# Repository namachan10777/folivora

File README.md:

# Folivora

Integrated ergonomics input device.

# Dependencies
 * KiCAD
 * OCaml
 * OpenSCAD

# License
MIT License

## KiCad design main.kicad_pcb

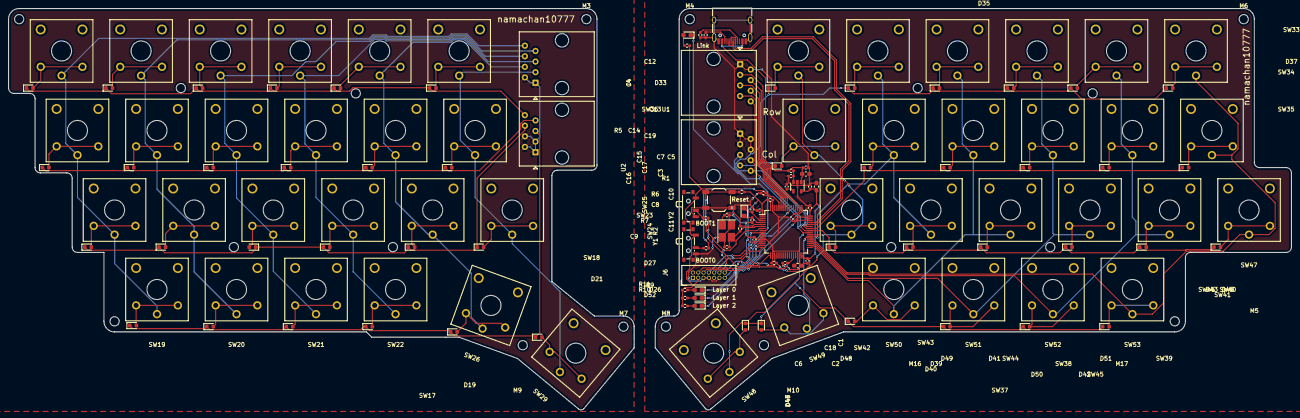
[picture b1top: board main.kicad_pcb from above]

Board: 2 copper layers, 307.3 x 96.1 mm, 161 parts (0 on the bottom side), 108 nets.

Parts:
C1, C3, C4, C5, C6, C7, C13, C14, C16, C18, C19: 0.1uF; C_0402_1005Metric_Pad0.74x0.62mm_HandSolder
C2, C12, C17: 4.7uF; C_0603_1608Metric_Pad1.08x0.95mm_HandSolder
C8, C9: 20pF; C_0402_1005Metric_Pad0.74x0.62mm_HandSolder
C10, C11: 12.5pF; C_0402_1005Metric_Pad0.74x0.62mm_HandSolder
C15: 0.1nF; C_0402_1005Metric_Pad0.74x0.62mm_HandSolder
D1, D2, D3, D4, D5, D6, D7, D8, D9, D10, D11, D12, D13, D14, D15, D16, D17, D18, D19, D20, D21, D22, D23, D24, D28, D29, D30, D31, D32, D33, D34, D35, D36, D37, D38, D39, D40, D41, D42, D43, D44, D45, D46, D47, D48, D49, D50, D51: D; D_0603_1608Metric
D25: LINKUP; LED_0603_1608Metric_Pad1.05x0.95mm_HandSolder
D26: L0; LED_0603_1608Metric_Pad1.05x0.95mm_HandSolder
D27: L1; LED_0603_1608Metric_Pad1.05x0.95mm_HandSolder
D52: L2; LED_0603_1608Metric_Pad1.05x0.95mm_HandSolder
J1, J2, J3, J4: RJ45; RJ45_Amphenol_54602-x08_Horizontal
J5: USB_C_Receptacle_USB2.0; USB_C_Receptacle_HRO_TYPE-C-31-M-12
J6: STLinkV3; IDC-Header_2x07_P1.27mm_Vertical
M1, M2, M3, M4, M5, M6, M7, M8, M9, M10, M11, M12, M13, M14, M15, M16, M17: MountingHole_2.2mm_M2
M20: MountingHole_2.2mm_M; MountingHole_2.2mm_M2
R1, R5, R6, R7: 10kohm; R_0402_1005Metric_Pad0.72x0.64mm_HandSolder
R2: 10Mohm; R_0402_1005Metric_Pad0.72x0.64mm_HandSolder
R3, R4: 5.1kohm; R_0402_1005Metric_Pad0.72x0.64mm_HandSolder
R8, R9, R10, R11: 220ohm; R_0402_1005Metric_Pad0.72x0.64mm_HandSolder
SW1: K11; Kailh_choc_V2
SW2: K21; Kailh_choc_V2
SW3: K31; Kailh_choc_V2
SW4: K41; Kailh_choc_V2
SW5: K51; Kailh_choc_V2
SW6: K61; Kailh_choc_V2
SW7: K12; Kailh_choc_V2
SW8: K22; Kailh_choc_V2
SW9: K32; Kailh_choc_V2
SW10: K42; Kailh_choc_V2
SW11: K52; Kailh_choc_V2
SW12: K62; Kailh_choc_V2
SW13: K13; Kailh_choc_V2
SW14: K23; Kailh_choc_V2
SW15: K33; Kailh_choc_V2
SW16: K43; Kailh_choc_V2
SW17: K53; Kailh_choc_V2
SW18: K63; Kailh_choc_V2
SW19: K14; Kailh_choc_V2
SW20: K24; Kailh_choc_V2
SW21: K34; Kailh_choc_V2
SW22: K44; Kailh_choc_V2
SW23: RST; SW_SPST_TL3342
SW24: BOOT0; SW_SPDT_PCM12
SW25: BOOT1; SW_SPDT_PCM12
SW26: K54; Kailh_choc_V2
SW29: K64; Kailh_choc_V2
SW30: K71; Kailh_choc_V2
SW31: K81; Kailh_choc_V2
SW32: K91; Kailh_choc_V2
SW33: K101; Kailh_choc_V2
SW34: K111; Kailh_choc_V2
SW35: K121; Kailh_choc_V2
SW36: K72; Kailh_choc_V2
SW37: K82; Kailh_choc_V2
SW38: K92; Kailh_choc_V2
SW39: K102; Kailh_choc_V2
SW40: K112; Kailh_choc_V2
SW41: K122; Kailh_choc_V2
SW42: K73; Kailh_choc_V2
SW43: K83; Kailh_choc_V2
SW44: K93; Kailh_choc_V2
SW45: K103; Kailh_choc_V2
SW46: K113; Kailh_choc_V2
SW47: K123; Kailh_choc_V2
SW48: K74; Kailh_choc_V2
SW49: K84; Kailh_choc_V2
SW50: K94; Kailh_choc_V2
SW51: K104; Kailh_choc_V2
SW52: K114; Kailh_choc_V2
SW53: K124; Kailh_choc_V2
U1: STM32F401RETx; LQFP-64_10x10mm_P0.5mm
U2: AP131-33; SOT-23-5
Y1: 8MHz; Crystal_SMD_SeikoEpson_TSX3225-4Pin_3.2x2.5mm_HandSoldering
Y2: 32.768kHz; Crystal_SMD_2012-2Pin_2.0x1.2mm_HandSoldering

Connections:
+3V3: C1.2, C3.2, C4.2, C5.2, C6.2, C7.2, C16.1, C17.1, J6.3, R1.1, R8.1, R9.1, R10.1, R11.1, SW24.1, SW25.1, U1.1, U1.13, U1.19, U1.32, U1.48, U1.64, U2.5
+5V: C12.1, C13.1, J5.A4, J5.A9, J5.B4, J5.B9, R5.1, U2.1
/8MHz_IN: C8.1, R2.2, U1.5, Y1.1
/8MHz_OUT: C9.1, R2.1, U1.6, Y1.3
/32.768kHz_IN: C10.1, U1.3, Y2.1
/32.768kHz_OUT: C11.1, U1.4, Y2.2
/BOOT0: C19.1, R7.2, U1.60
/BOOT1: C18.1, R6.2, U1.28
/COL1: J1.8, U1.59
/COL2: J1.7, U1.58
/COL3: J1.6, U1.57
/COL4: J1.5, U1.56
/COL5: J1.4, U1.52
/COL6: J1.3, U1.51
/COL7: SW30.1, SW36.1, SW42.1, SW48.1, U1.39
/COL8: SW31.1, SW37.1, SW43.1, SW49.1, U1.38
/COL9: SW32.1, SW38.1, SW44.1, SW50.1, U1.34
/COL10: SW33.1, SW39.1, SW45.1, SW51.1, U1.35
/COL11: SW34.1, SW40.1, SW46.1, SW52.1, U1.36
/COL12: SW35.1, SW41.1, SW47.1, SW53.1, U1.37
/D+: J5.A6, J5.B6, U1.45
/D-: J5.A7, J5.B7, U1.44
/DEBUG_RX: J6.14, U1.17
/DEBUG_TX: J6.13, U1.16
/JTCK: J6.6, U1.49
/JTDI: J6.10, U1.50
/JTDO: J6.8, U1.55
/JTMS: J6.4, U1.46
/LAYER0: D26.1, U1.9
/LAYER1: D27.1, U1.14
/LAYER2: D52.1, U1.15
/LINKUP: D25.1, U1.8
/ROW1: D23.1, D28.1, D29.1, D30.1, D31.1, D32.1, J4.8, U1.43
/ROW2: D33.1, D34.1, D35.1, D36.1, D37.1, D38.1, J4.7, U1.42
/ROW3: D39.1, D40.1, D41.1, D42.1, D43.1, D45.1, J4.6, U1.41
/ROW4: D46.1, D47.1, D48.1, D49.1, D50.1, D51.1, J4.5, U1.40
/RST: J6.12, R1.2, SW23.2, U1.7
GND: C1.1, C2.2, C3.1, C4.1, C5.1, C6.1, C7.1, C8.2, C9.2, C10.2, C11.2, C12.2, C13.2, C14.2, C15.2, C16.2, C17.2, C18.2, C19.2, J1.1, J1.2, J4.1, J4.2, J4.3, J4.4, J5.A1, J5.A12, J5.B1, J5.B12, J5.S1, J6.5, J6.7, J6.11, R3.2, R4.2, SW23.1, SW24.3, SW25.3, U1.12, U1.18, U1.31, U1.47, U1.63, U2.2, Y1.2, Y1.4
GND1: J2.1, J2.2, J3.1, J3.2, J3.3, J3.4
unnamed: C2.1, U1.30
unnamed: C14.1, R5.2, U2.3
unnamed: C15.1, U2.4
unnamed: D1.1, D2.1, D3.1, D4.1, D5.1, D6.1, J3.8
unnamed: D1.2, SW1.2
unnamed: D2.2, SW2.2
unnamed: D3.2, SW3.2
unnamed: D4.2, SW4.2
unnamed: D5.2, SW5.2
unnamed: D6.2, SW6.2
unnamed: D7.2, SW7.2
unnamed: D8.2, SW8.2
unnamed: D9.2, SW9.2
unnamed: D7.1, D8.1, D9.1, D10.1, D11.1, D12.1, J3.7
unnamed: D10.2, SW10.2
unnamed: D11.2, SW11.2
unnamed: D12.2, SW12.2
unnamed: D13.1, D14.1, D15.1, D16.1, D17.1, D18.1, J3.6
unnamed: D13.2, SW13.2
unnamed: D14.2, SW14.2
unnamed: D15.2, SW15.2
unnamed: D16.2, SW16.2
unnamed: D17.2, SW17.2
unnamed: D18.2, SW18.2
unnamed: D19.1, D20.1, D21.1, D22.1, D24.1, D44.1, J3.5
unnamed: D19.2, SW26.2
unnamed: D20.2, SW19.2
unnamed: D21.2, SW29.2
unnamed: D22.2, SW20.2
unnamed: D23.2, SW30.2
unnamed: D24.2, SW21.2
unnamed: D25.2, R8.2
unnamed: D26.2, R9.2
unnamed: D27.2, R10.2
unnamed: D28.2, SW31.2
unnamed: D29.2, SW32.2
unnamed: D30.2, SW33.2
unnamed: D31.2, SW34.2
unnamed: D32.2, SW35.2
unnamed: D33.2, SW36.2
unnamed: D34.2, SW37.2
unnamed: D35.2, SW38.2
unnamed: D36.2, SW39.2
unnamed: D37.2, SW40.2
unnamed: D38.2, SW41.2
unnamed: D39.2, SW42.2
unnamed: D40.2, SW43.2
unnamed: D41.2, SW44.2
unnamed: D42.2, SW45.2
unnamed: D43.2, SW46.2
unnamed: D44.2, SW22.2
unnamed: D45.2, SW47.2
unnamed: D46.2, SW48.2
unnamed: D47.2, SW49.2
unnamed: D48.2, SW50.2
unnamed: D49.2, SW51.2
unnamed: D50.2, SW52.2
unnamed: D51.2, SW53.2
unnamed: D52.2, R11.2
unnamed: J2.3, SW6.1, SW12.1, SW18.1, SW29.1
unnamed: J2.4, SW5.1, SW11.1, SW17.1, SW26.1
unnamed: J2.5, SW4.1, SW10.1, SW16.1, SW22.1
unnamed: J2.6, SW3.1, SW9.1, SW15.1, SW21.1
unnamed: J2.7, SW2.1, SW8.1, SW14.1, SW20.1
unnamed: J2.8, SW1.1, SW7.1, SW13.1, SW19.1
unnamed: J5.A5, R4.1
unnamed: J5.B5, R3.1
unnamed: R6.1, SW25.2
unnamed: R7.1, SW24.2

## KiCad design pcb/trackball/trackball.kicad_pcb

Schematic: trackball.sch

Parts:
C1, C3, C4, C5: 0.1uF; C_0603_1608Metric
J1: 5V; TestPoint_THTPad_D1.0mm_Drill0.5mm
J2: UP; TestPoint_THTPad_D1.0mm_Drill0.5mm
J3: R; TestPoint_THTPad_D1.0mm_Drill0.5mm
J4: D; TestPoint_THTPad_D1.0mm_Drill0.5mm
J5: L; TestPoint_THTPad_D1.0mm_Drill0.5mm
J7: GND; TestPoint_THTPad_D1.0mm_Drill0.5mm
R6, R7, R8, R9: 10k; R_0603_1608Metric
U1, U2, U3, U4: AN48841B; SMINI_5DE

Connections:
+5V: C1.1, C3.1, C4.1, C5.1, J1.1, R6.1, R7.1, R8.1, R9.1, U1.4 (Vcc), U2.4 (Vcc), U3.4 (Vcc), U4.4 (Vcc)
/DOWN: J4.1, R8.2, U3.5 (OUT)
/LEFT: J5.1, R9.2, U4.5 (OUT)
/RIGHT: J3.1, R7.2, U2.5 (OUT)
/UP: J2.1, R6.2, U1.5 (OUT)
GND: C1.2, C3.2, C4.2, C5.2, J7.1, U1.2 (GND), U2.2 (GND), U3.2 (GND), U4.2 (GND)

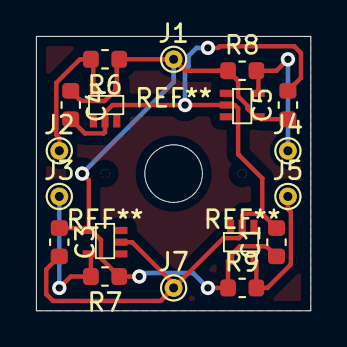
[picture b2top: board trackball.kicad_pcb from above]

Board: 2 copper layers, 15.2 x 15.2 mm, 18 parts (0 on the bottom side), 6 nets.

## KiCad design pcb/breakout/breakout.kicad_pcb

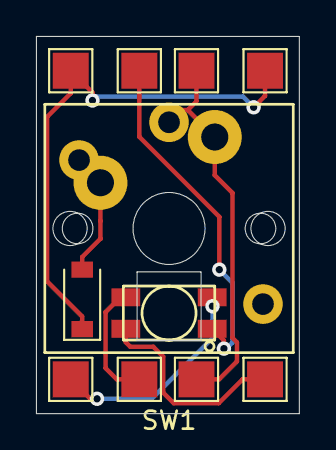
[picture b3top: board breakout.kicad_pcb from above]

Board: 2 copper layers, 14.6 x 21.0 mm, 11 parts (0 on the bottom side), 7 nets.

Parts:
D1: D; D_SOD-123
SW1: Key; MX_KailhLP
TP1: DIN; TestPoint_Pad_2.0x2.0mm
TP2: Vdd; TestPoint_Pad_2.0x2.0mm
TP3: GND; TestPoint_Pad_2.0x2.0mm
TP4, TP5: READ; TestPoint_Pad_2.0x2.0mm
TP6, TP7: SELECT; TestPoint_Pad_2.0x2.0mm
TP8: DOUT; TestPoint_Pad_2.0x2.0mm
U1: SK6812; SK6812MINI_rev

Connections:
unnamed: D1.1, TP6.1, TP7.1
unnamed: D1.2, SW1.1
unnamed: SW1.2, TP4.1, TP5.1
unnamed: TP1.1, U1.2
unnamed: TP2.1, U1.3
unnamed: TP3.1, U1.1
unnamed: TP8.1, U1.4

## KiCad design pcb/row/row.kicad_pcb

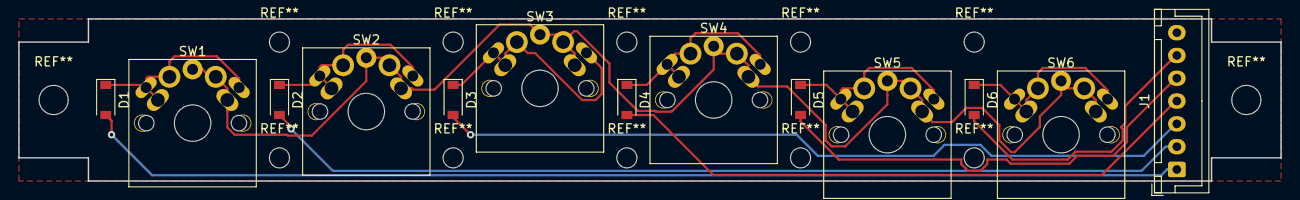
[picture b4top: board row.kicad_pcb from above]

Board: 2 copper layers, 138.4 x 17.8 mm, 13 parts (0 on the bottom side), 13 nets.

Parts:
D1: D0; D_SOD-123
D2: D1; D_SOD-123
D3: D2; D_SOD-123
D4: D3; D_SOD-123
D5: D4; D_SOD-123
D6: D5; D_SOD-123
J1: INTERFACE; JST_XH_B07B-XH-A_1x07_P2.50mm_Vertical
SW1: SW0; SW_Cherry_MX1A_1.00u_PCB
SW2: SW1; SW_Cherry_MX1A_1.00u_PCB
SW3: SW2; SW_Cherry_MX1A_1.00u_PCB
SW4: SW3; SW_Cherry_MX1A_1.00u_PCB
SW5: SW4; SW_Cherry_MX1A_1.00u_PCB
SW6: SW5; SW_Cherry_MX1A_1.00u_PCB

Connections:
/READ0: D1.2, J1.1
/READ1: D2.2, J1.2
/READ2: D3.2, J1.3
/READ3: D4.2, J1.4
/READ4: D5.2, J1.5
/READ5: D6.2, J1.6
/SELECT: J1.7, SW1.2, SW2.2, SW3.2, SW4.2, SW5.2, SW6.2
unnamed: D1.1, SW1.1
unnamed: D2.1, SW2.1
unnamed: D3.1, SW3.1
unnamed: D4.1, SW4.1
unnamed: D5.1, SW5.1
unnamed: D6.1, SW6.1

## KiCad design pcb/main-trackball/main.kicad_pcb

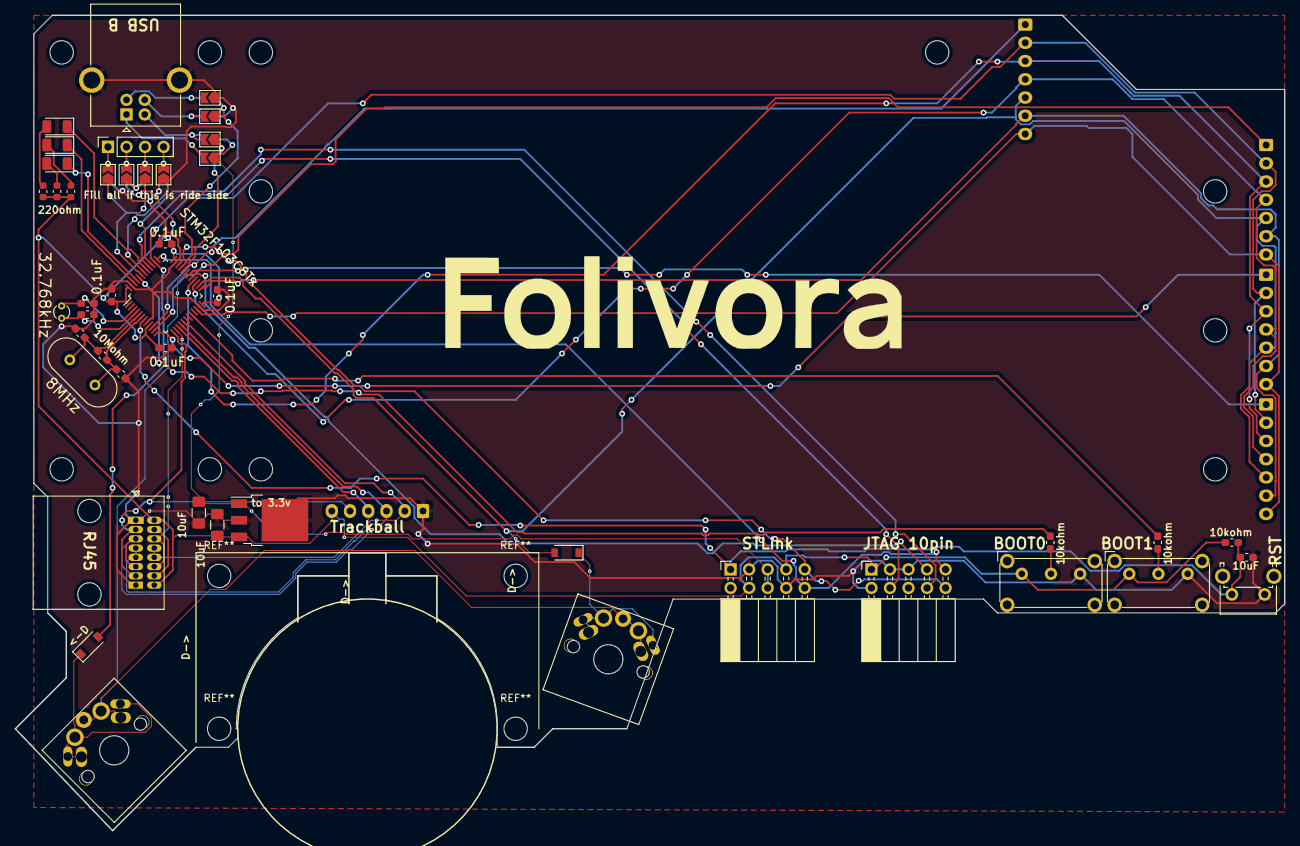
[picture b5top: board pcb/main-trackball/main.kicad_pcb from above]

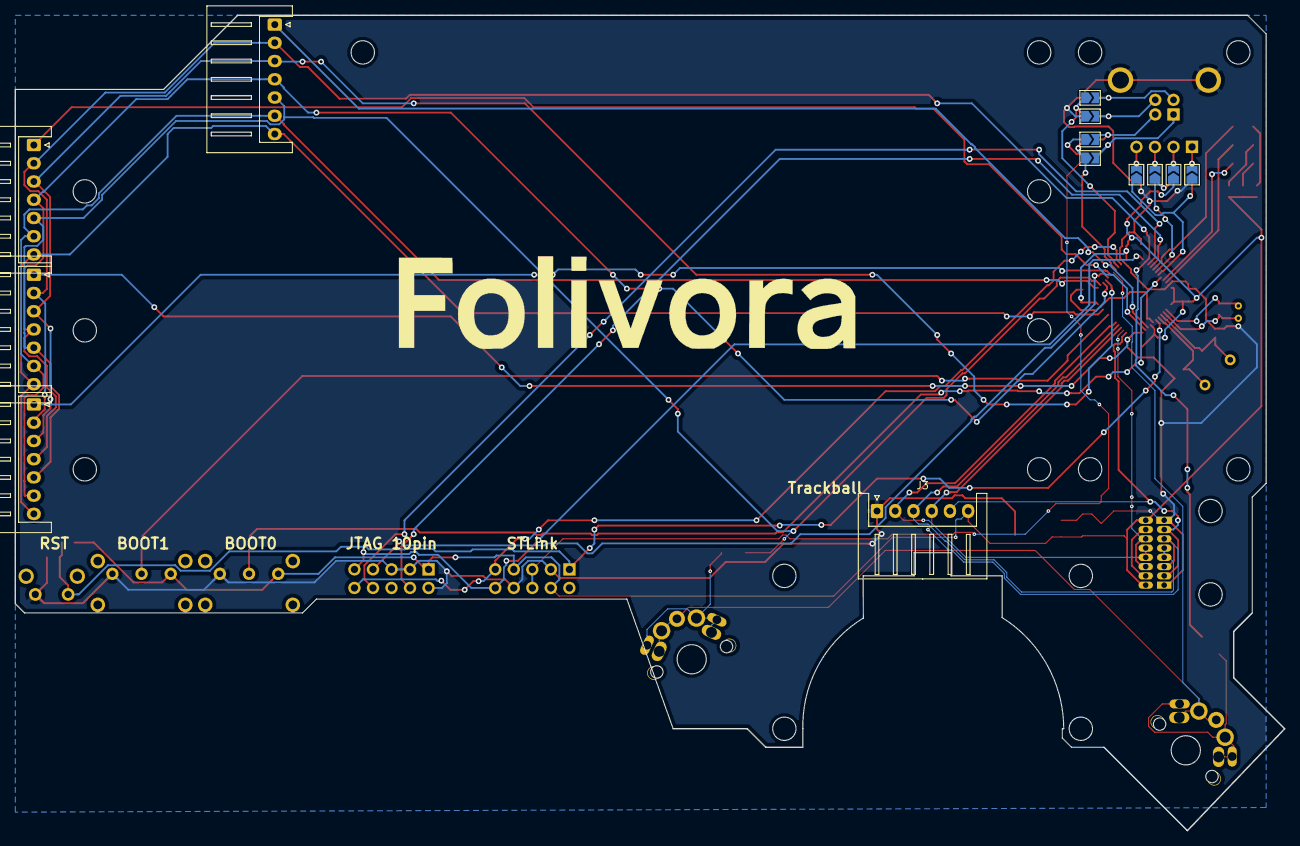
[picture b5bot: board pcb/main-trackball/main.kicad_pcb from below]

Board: 2 copper layers, 174.0 x 111.8 mm, 58 parts (13 on the bottom side), 53 nets.

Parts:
C1, C2: 10uF; C_1206_3216Metric_Pad1.42x1.75mm_HandSolder
C3: 12.5pF; C_0603_1608Metric_Pad1.05x0.95mm_HandSolder
C4: 12.5pF[; C_0603_1608Metric_Pad1.05x0.95mm_HandSolder
C5, C6: 20pF; C_0603_1608Metric_Pad1.05x0.95mm_HandSolder
C7: 10uF; C_0603_1608Metric_Pad1.05x0.95mm_HandSolder
C8, C9, C10, C11: 0.1uF; C_0603_1608Metric_Pad1.05x0.95mm_HandSolder
D1, D4: D; D_SOD-123
D5, D6, D7: LED; LED_1206_3216Metric
J1: Conn_01x04; PinSocket_1x04_P2.54mm_Vertical
J2: USB_B; USB_B_OST_USB-B1HSxx_Horizontal
J3: Trackball_conn; JST_XH_S06B-XH-A_1x06_P2.50mm_Horizontal
J4: ROW0; JST_XH_S07B-XH-A_1x07_P2.50mm_Horizontal
J5: RJ45; RJ45_rev
J6: ROW1; JST_XH_S07B-XH-A_1x07_P2.50mm_Horizontal
J7: ROW2; JST_XH_S07B-XH-A_1x07_P2.50mm_Horizontal
J8: ROW3; JST_XH_S07B-XH-A_1x07_P2.50mm_Horizontal
J9: STLink; PinSocket_2x05_P2.54mm_Horizontal
J10: JTAG; PinSocket_2x05_P2.54mm_Horizontal
JP2, JP4, JP6, JP8, JP11, JP13, JP15, JP17: L; SolderJumper-2_P1.3mm_Open_TrianglePad1.0x1.5mm
JP3, JP5, JP7, JP9, JP10, JP12, JP14, JP16: R; SolderJumper-2_P1.3mm_Open_TrianglePad1.0x1.5mm
R1, R2, R3: R; R_0603_1608Metric
R4: 10Mohm; R_0603_1608Metric_Pad1.05x0.95mm_HandSolder
R5, R6, R7: 10kohm; R_0603_1608Metric_Pad1.05x0.95mm_HandSolder
SW1: SW40; SW_Cherry_MX1A_1.00u_PCB
SW4: SW43; SW_Cherry_MX1A_1.00u_PCB
SW5: RST_SW; SW_Tactile_SPST_Angled_PTS645Vx31-2LFS
SW6: BOOT0; SW_E-Switch_EG1224_SPDT_Angled
SW7: BOOT1; SW_E-Switch_EG1224_SPDT_Angled
U1: 3.3v regul; TO-252-3_TabPin2
U2: STM32F103C8Tx; LQFP-48_7x7mm_P0.5mm
Y1: 32.768kHz; Crystal_DS15_D1.5mm_L5.0mm_Vertical
Y2: 8MHz; Crystal_HC49-U_Vertical

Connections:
+3V3: C2.1, C8.1, C9.1, C10.1, C11.1, J3.6, J5.8, J9.4, J9.7, J10.1, JP12.1, JP15.1, R1.1, R2.1, R3.1, R5.2, SW6.1, SW7.1, U1.3, U2.1, U2.9, U2.24, U2.36, U2.48
+5V: C1.1, J9.5, J9.6, JP3.1, JP4.1, U1.1
/BOOT0: R6.2, U2.44
/BOOT1: R7.2, U2.20
/D+: JP7.1, JP8.1, U2.33
/D-: JP2.1, JP5.1, U2.32
/JNTRST: J10.4, U2.40
/JTDI: J10.7, U2.29
/JTDO: J10.8, U2.39
/LED1: D5.1, U2.45
/LED2: D6.1, U2.46
/LED3: D7.1, U2.41
/MISO: J3.3, J5.5, U2.16
/MOSI: J3.2, J5.4, U2.17
/OLED1: J1.1, JP10.2, JP11.2
/OLED2: J1.2, JP12.2, JP13.2
/OLED3: J1.3, JP14.2, JP15.2
/OLED4: J1.4, JP16.2, JP17.2
/READ0: D1.2, J4.2, J6.2, J7.2, J8.2, U2.38
/READ1: J4.3, J6.3, J7.3, J8.3, U2.28
/READ2: J4.4, J6.4, J7.4, J8.4, U2.27
/READ3: D4.2, J4.5, J6.5, J7.5, J8.5, U2.26
/READ4: J4.6, J6.6, J7.6, J8.6, U2.25
/READ5: J4.7, J6.7, J7.7, J8.7, U2.22
/RST: C7.1, J9.1, R5.1, SW5.2, U2.7
/SCK: J3.4, J5.3, U2.15
/SCL: JP13.1, JP14.1, U2.42
/SDA: JP11.1, JP16.1, U2.43
/SELECT0: J4.1, U2.10
/SELECT1: J6.1, U2.11
/SELECT2: J7.1, U2.12
/SELECT3: J8.1, U2.30
/SELECT4: SW1.2, SW4.2, U2.31
/SS_K: J5.6, U2.14
/SS_T: J3.5, J5.7, U2.13
/SWCLK: J9.10, J10.9, U2.37
/SWDIO: J9.9, J10.10, U2.34
/USB_1: J2.1, JP2.2, JP3.2
/USB_2: J2.2, JP4.2, JP5.2
/USB_3: J2.3, JP6.2, JP7.2
/USB_4: J2.4, JP8.2, JP9.2
/XTAL_A: C5.2, R4.2, U2.5, Y2.2
/XTAL_B: C6.2, R4.1, U2.6, Y2.1
/XTAL_C: C3.2, U2.3, Y1.2
/XTAL_D: C4.2, U2.4, Y1.1
GND: C1.2, C2.2, C3.1, C4.1, C5.1, C6.1, C7.2, C8.2, C9.2, C10.2, C11.2, J2.5, J3.1, J5.1, J9.3, J9.8, J10.2, J10.3, J10.5, JP6.1, JP9.1, JP10.1, JP17.1, SW5.1, SW6.3, SW7.3, U1.2, U2.8, U2.23, U2.35, U2.47
unnamed: D1.1, SW1.1
unnamed: D4.1, SW4.1
unnamed: D5.2, R1.2
unnamed: D6.2, R2.2
unnamed: D7.2, R3.2
unnamed: R6.1, SW6.2
unnamed: R7.1, SW7.2

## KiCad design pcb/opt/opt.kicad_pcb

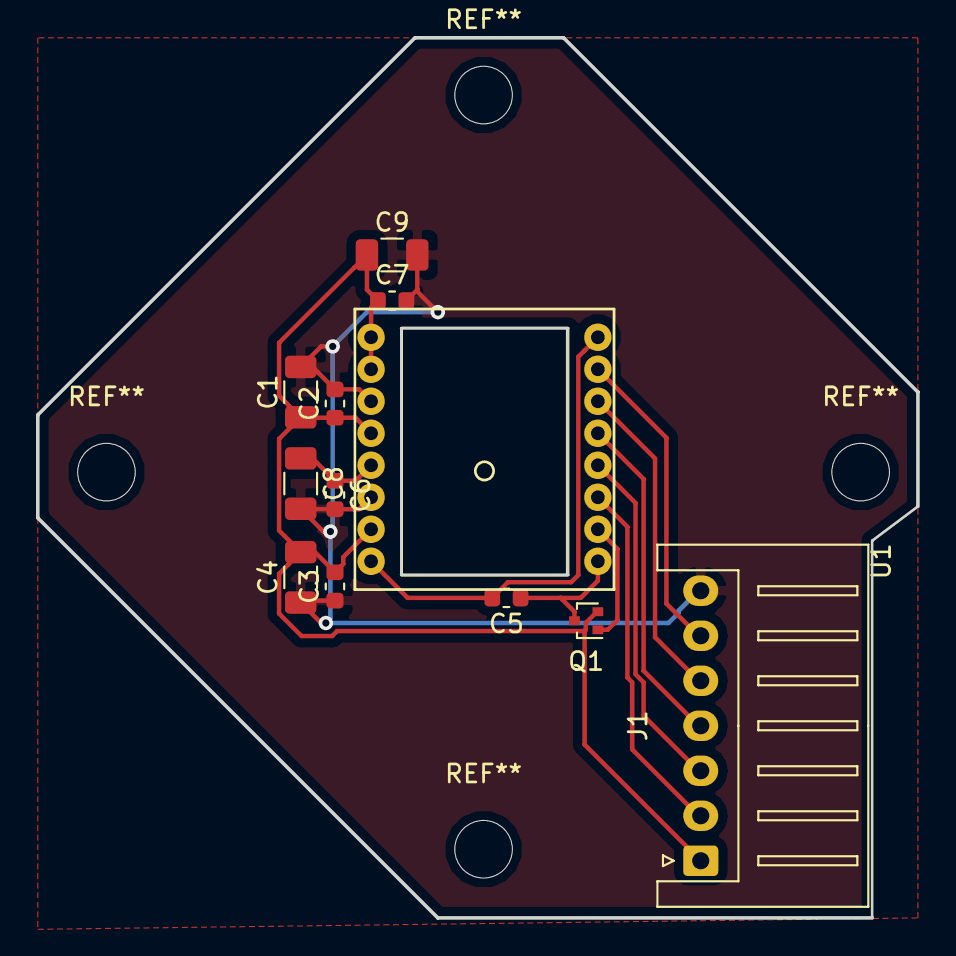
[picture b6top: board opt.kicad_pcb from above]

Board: 2 copper layers, 48.9 x 48.9 mm, 12 parts (0 on the bottom side), 11 nets.

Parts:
C1: 3.3uF; C_1206_3216Metric
C2, C3, C7: 100nF; C_0603_1608Metric
C4, C8: 10uF; C_1206_3216Metric
C5: 470pF; C_0603_1608Metric
C6: 100uF; C_0603_1608Metric
C9: 1uF; C_1206_3216Metric
J1: INTERFACE; JST_XH_S07B-XH-A_1x07_P2.50mm_Horizontal
Q1: Q_PMOS_GDS; SOT-416
U1: ADNS-9800

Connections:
+3V3: C1.1, C2.1, C3.2, C4.2, C7.1, C9.1, J1.1, Q1.2, U1.9, U1.10, U1.12, U1.15
GND: C1.2, C2.2, C3.1, C4.1, C6.2, C7.2, C8.2, C9.2, J1.7, U1.11, U1.14
unnamed: C5.1, Q1.3, U1.1
unnamed: C5.2, U1.8, U1.16
unnamed: C6.1, C8.1, U1.13
unnamed: J1.2, U1.3
unnamed: J1.3, U1.4
unnamed: J1.4, U1.5
unnamed: J1.5, U1.6
unnamed: J1.6, U1.7
unnamed: Q1.1, U1.2

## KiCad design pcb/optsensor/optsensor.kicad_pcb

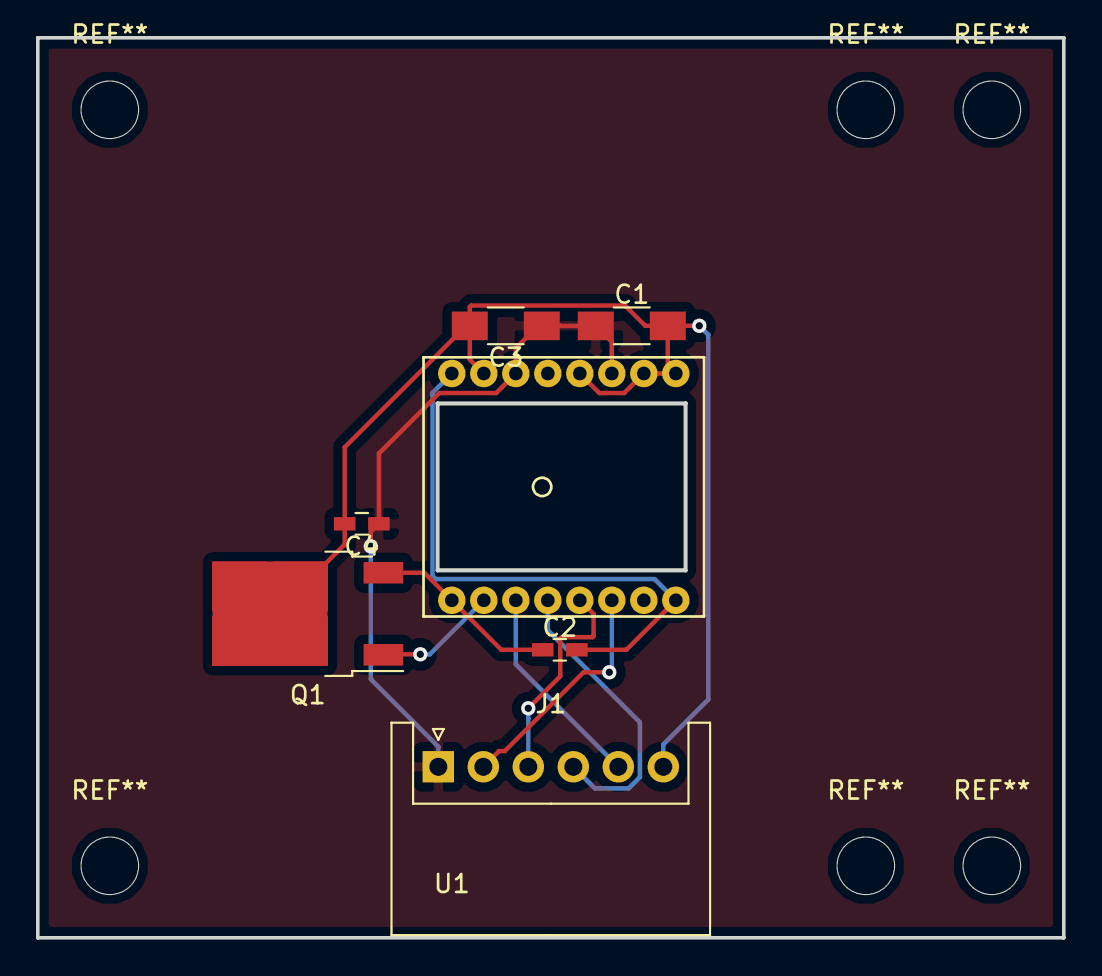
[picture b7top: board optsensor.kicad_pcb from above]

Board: 2 copper layers, 57.0 x 50.0 mm, 7 parts (0 on the bottom side), 9 nets.

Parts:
C1, C3: 10uF; C_1206_HandSoldering
C2: 470pF; C_0603_HandSoldering
C4: 1uF; C_0603_HandSoldering
J1: XH6; JST_XH_S06B-XH-A_06x2.50mm_Angled
Q1: Q_PMOS_GDS; TO-252-2
U1: ADNS-9800

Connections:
+3V3: C1.2, C3.2, C4.2, J1.6, Q1.2, U1.9, U1.10, U1.12, U1.15
GND: C1.1, C3.1, C4.1, J1.1, U1.11, U1.14
unnamed: C2.1, Q1.3, U1.1
unnamed: C2.2, U1.8, U1.16
unnamed: J1.2, U1.6
unnamed: J1.3, U1.5
unnamed: J1.4, U1.4
unnamed: J1.5, U1.3
unnamed: Q1.1, U1.2

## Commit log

2018-06-03 add mechanical design
2018-07-06 update mechanical design
2018-07-20 設計の整理
2018-07-21 左手側を追加
2018-07-21 どうにかしてセンサー設置空間を確保
    妥協と諦め
2018-07-22 インターフェース設置用の穴を開けた
2018-07-22 add optsensor pcb
2018-07-27 左右対称なデザイン
2018-07-27 add drawings
2018-07-27 update gitignore
2018-07-28 add part of catting pattern
2018-07-28 improve palmrest
2018-07-29 extend key
2018-07-29 down palmrest
2018-07-30 secure space for main pcb
2018-07-30 palmrestとキーの間に空間を設ける
2018-08-10 revision design
    生産性の向上
2018-09-18 add main schematic
2018-09-18 fix directory structure
2018-09-18 remove regacy files
2018-09-18 determine circuit constant
2018-09-18 add XH6 to connect trackball
2018-09-18 impl main pcb
2018-09-22 fix main pcb
2018-09-22 ignore backup file
2018-09-22 update optsensor schematic
2018-10-31 3d: add base
2018-11-01 add trackball anhorage
2018-11-04 improve naming of 3d/top.scad
2018-11-04 add bearing_cover
2018-11-04 add ball_cover
2018-11-05 add screw hole to ball cover
2018-11-05 add bearing_base.scad
2018-11-05 fix warning of top.scad
2018-11-05 fix inside out
2018-11-05 add bearing_base to top.scad
2018-11-05 add anchorage to trackball bridge
2018-11-10 fix trackball design
2018-11-22 reduce bearing module size
2018-11-30 Hello clojure!
2018-12-08 add key-elm
2018-12-08 impl joint
2018-12-14 improve util functions
2018-12-23 improve center-move-vec
2018-12-24 fix key-elm-pos
2018-12-24 add key-col
2018-12-28 fix util/vecop
2018-12-28 improve key-col and assistant functions
2019-01-13 impl padding for key joint
2019-01-26 add lib
2019-01-26 add watcher
2019-01-26 ignore *.scad
2019-01-27 update scad_ml
2019-01-27 add key_elm
2019-01-27 impl key_col
2019-01-27 recompile when any .ml file be modified
2019-01-30 impl joint padding
2019-02-09 3d: refactoring sidewall
2019-02-09 3d: add joint sidewall
2019-02-10 3d: fix key_joint_pos
2019-02-10 impl key_col_padding
2019-02-12 add block.ml
2019-02-16 impl block
2019-02-16 mechanical design
2019-02-16 fix block thickness
2019-02-17 production!
2019-02-20 add bearing_hole
2019-02-20 impl bearing_holes
2019-02-20 impl under_block
2019-02-20 add sphere hollowing to under block
2019-02-20 under_block take parameter only h
2019-02-20 refactor track.ml
2019-02-21 fix Track.foundation
2019-02-23 main pcb: fill
2019-02-23 add pcb opt
2019-02-23 tilt: start
2019-02-23 fix tilt
2019-02-23 add bearinghdge hollowing
2019-02-23 fix tilt foundation
2019-02-23 add screw_holes
2019-02-23 refactor foundation_body
2019-02-23 refactor foundation
2019-02-23 impl bearing_cover
2019-02-24 impl deploy code
2019-02-24 add docker container for build
2019-02-24 add ci config
2019-02-26 fix build.sh
2019-02-26 下から球が抜けるように
2019-02-26 add dependency to README.md
2019-02-26 improve trackball shape
2019-02-28 Track: for FDM
2019-03-04 最初の方
2019-03-08 utop -> ocaml
2019-03-08 fix Dockerfile
2019-03-08 fix bash path
2019-03-08 add zip to Docker
2019-03-08 improve intro
2019-03-08 make headlines
2019-03-08 ci: update submodules
2019-03-09 fix ci
2019-03-09 fix mkdir option
2019-03-09 ci: add store_artifacts
2019-03-09 ci: fix artifacts config
2019-03-09 add zip-pcb-files.sh
2019-03-09 ci: improve artifacts config
2019-03-09 config for anycubic i3 mega
2019-03-10 fix block for anycubic i3 mega
2019-03-10 fix circle ci destination setting
2019-03-10 for Φ2.5 axis
2019-03-10 actually, I use Φ3
2019-03-10 add trackball module for right-handed
2019-03-10 fix syntax
2019-03-10 diet
2019-03-11 fix slit size
2019-03-11 add clean.sh
2019-03-11 refactoring
2019-03-11 hollow for screw head
2019-03-11 for Φ12.5 sphere
2019-03-11 fix CE
2019-03-11 fix invalid model
2019-03-12 optimize slit size
2019-03-12 fix bearing cover tilt
2019-03-12 downsize trakball
2019-03-13 revise trackball
2019-03-13 add ball cover
2019-03-13 smoothing trackball module
2019-03-13 revise main pcb
2019-03-17 revise row
2019-03-18 complete sch
2019-03-18 fix blackpill lib
2019-03-18 arrange parts
2019-03-18 use STM32F103C8T6 directly
2019-03-19 keyboard pcb
2019-03-19 add main-trackball
2019-03-19 add design helper
2019-03-19 wiring
2019-03-20 fix design
2019-03-22 for Φ25
2019-03-22 slanting cut
2019-03-27 impl key.ml
2019-03-27 temporarily assembled wall
2019-03-27 reduce rib
2019-03-28 improve key module parameter
2019-03-28 screw holes for keymodule
2019-03-29 improve key module rigidity
2019-03-29 prepare operators
2019-03-29 remove block module
2019-03-29 use operators of common.ml
2019-03-29 X axis values are determined by inch
    This is so humiliating...
2019-03-29 infinit probability
2019-03-29 refactor key_pad
2019-03-30 refactor key_rib
2019-03-30 optimize keyhole shape
2019-03-31 fix wellhole_d
2019-04-02 impl thumb_key
2019-04-02 fix thumb_keys
2019-04-06 impl trackball_cover
2019-04-08 rename track -> thumb
2019-04-10 improve keypad
2019-04-11 flatten part of key_pad that is near side.
2019-04-11 origin adjustment
2019-04-12 joint thumb and pad
2019-04-13 add wall at far-side
2019-04-13 add clearance to wall
2019-04-14 complete walls
2019-04-14 add wire passage
2019-04-16 impl plate
2019-04-16 refactor key.ml
2019-04-17 impl pad
2019-04-18 fix compile script
2019-04-18 add mov_block
2019-04-18 improve mov_block
2019-04-18 expand params to near side
2019-04-18 fix bond
2019-04-20 add len_wall
2019-04-20 impl auto wall thickening
2019-04-21 impl prevent_near_wall
2019-04-21 impl row_wall
2019-07-22 add blackberry trackball parts
2019-07-22 refactor 3d model
2019-07-23 complete trackball breakout
2019-07-27 trackball breakout
2019-07-27 add pad edge
2019-07-27 add thumb side edge
2019-07-27 prepare to define bridge between pad and thumb
2019-07-28 thumb bridge
2019-07-29 add screw_mount
2019-07-29 revision README
2019-07-30 rm pcbs
2019-07-30 add plate
2019-07-30 export full model resources
2019-07-31 improve circuit board mount point
2019-07-31 add docker badge
2019-07-31 manual scaling circuit board.
2019-08-03 change BlackPill footprint non-reversible
2019-08-03 optimized electrical board space
2019-08-03 integrate gitignore
2019-08-03 complete pcb design
2019-08-03 resize main pcb
2019-08-03 hollow cable tunnel
2019-08-03 production pcb
2019-08-03 add Micro_hole footprint
2020-06-22 make!
2020-06-22 fix circleci config
2020-06-22 add -C 3d
2020-06-22 update Dockerfile
2020-06-22 opam config env
2020-06-22 explicit ocamlrun
2020-06-22 update ubuntu
2020-06-30 remove scad_ml
2020-06-30 dune build
2020-06-30 update opam
2020-06-30 read scad_ml
2020-06-30 add cherry_mx_unit
2020-06-30 kailh lp
2020-06-30 Docker includes scad_ml
2020-07-04 thumb model
2020-07-10 define pad.f signature
2020-07-13 parametric curve
2020-09-19 place columns
2020-09-29 gen_center_with_bridge
2020-10-09 remove 3d/
2020-10-09 add matrix module
2020-10-09 indexed flexible placing
2020-10-09 padding on
2020-10-10 joint
2020-10-10 full joint
2020-10-12 configure main pad
2020-10-12 enable reverse bending
2020-10-17 wrist-switch
2020-10-24 reset
2020-10-24 organize
2020-10-24 next-gen
2020-10-25 xy-horizontal
2020-10-28 skelton
2020-10-29 joint top
2020-10-30 flexible pad
2020-11-01 fix pcb
2020-11-01 pcb inserted
2020-11-01 insert patch
2020-11-01 add screw point
2020-11-03 add screws
2020-11-06 imporve OLED profile
2020-11-06 simplify model
2020-11-06 split to 3 modules
2020-11-06 adjust moutings
2020-11-06 screw bottom top_cut
2020-11-06 pcb update
2020-11-06 remove 3d directory
2020-11-07 design key profiles
2020-11-16 test
2020-11-16 compact
2020-11-26 redesign pcb
2020-11-27 finish
2020-11-27 fix RJ45 placing
2020-11-29 fix connector
2021-01-01 fix Makefile: enable parallel build
2021-01-01 docker: install jane street core
2021-01-22 adjust screw position
2021-01-22 fix scad file names and remove unnecessary union()
2021-01-23 fix key spacing
2021-01-23 fix key_unit
2021-01-23 fix screw position
2021-01-23 adjust screw positions
2021-01-23 thin kp
2021-01-25 fix plane
2021-02-04 fix screw
2021-02-04 ocamlformat
2021-02-04 adjust kp
2021-02-05 adjust
2021-02-07 人差し指遠かった
2021-02-07 adjust screw
2021-02-07 fix screws
2021-02-14 fix kt
2021-02-14 キーボードってなんだ？
2021-02-14 small thumb pad
2021-02-21 flat
2021-02-23 palmrest
2021-02-23 weight space
2021-03-05 flat key
2021-03-06 right-hand
2021-03-09 shape
2021-03-12 redesign
2021-03-12 pcb only
2021-03-12 remove lib
2021-03-12 clean folivora/pretty
2021-03-12 complete ver
2021-03-12 adjust silks
